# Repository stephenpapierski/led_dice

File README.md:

# led_dice
Embedded code for an LED dice running on an ATtiny85

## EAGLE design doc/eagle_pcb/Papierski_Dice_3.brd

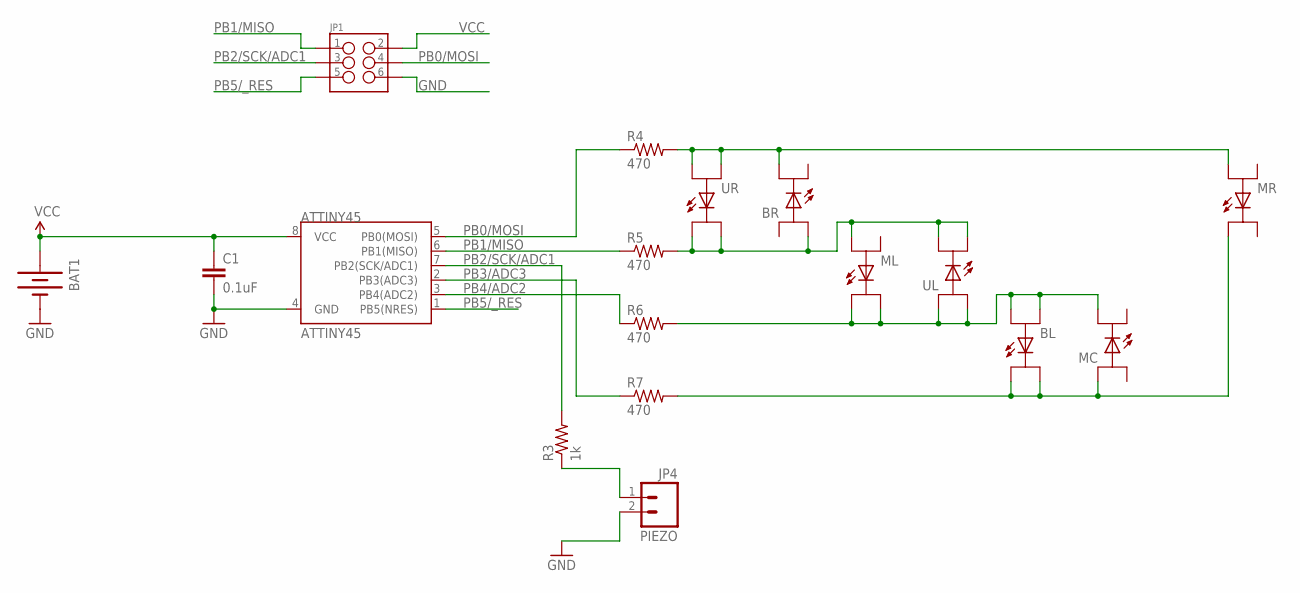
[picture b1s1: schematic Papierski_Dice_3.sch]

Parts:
ATTINY45: ATTINY45; SO08-EIAJ
BAT1: BATTERY20PTH; BATTCOM_20MM_PTH
BL: LED_PIRANHA_5MM_SNGLS; LED_PIRANHA_5MM_SNGL_SMD
BR: LED_PIRANHA_5MM_SNGLS; LED_PIRANHA_5MM_SNGL_SMD
C1: 0.1uF; 0805
JP1: M03X2NO_SILK; 2X3-NS
MC: LED_PIRANHA_5MM_SNGLS; LED_PIRANHA_5MM_SNGL_SMD
ML: LED_PIRANHA_5MM_SNGLS; LED_PIRANHA_5MM_SNGL_SMD
MR: LED_PIRANHA_5MM_SNGLS; LED_PIRANHA_5MM_SNGL_SMD
PIEZO: JP4; 1X02
R3: 1k; AXIAL-0.3
R4, R5, R6: 470; AXIAL-0.3
R7: 470; 0805
UL: LED_PIRANHA_5MM_SNGLS; LED_PIRANHA_5MM_SNGL_SMD
UR: LED_PIRANHA_5MM_SNGLS; LED_PIRANHA_5MM_SNGL_SMD

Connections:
GND: ATTINY45.4 (GND), BAT1.2 (-), C1.2, JP1.6, PIEZO.2
unnamed: BR.K1 (C1), MR.A1, R4.P$2 (2), UR.A1, UR.A2
unnamed: BL.A1, BL.A2, MC.K1 (C1), ML.K1 (C1), ML.K2 (C2), R6.P$2 (2), UL.A1, UL.A2
unnamed: BL.K1 (C1), BL.K2 (C2), MC.A2, MR.K2 (C2), R7.2
unnamed: PIEZO.1, R3.P$1 (1)
unnamed: BR.A1, ML.A1, R5.P$2 (2), UL.K1 (C1), UL.K2 (C2), UR.K1 (C1), UR.K2 (C2)
PB0/MOSI: ATTINY45.5 (PB0(MOSI)), JP1.4, R4.P$1 (1)
PB1/MISO: ATTINY45.6 (PB1(MISO)), JP1.1, R5.P$1 (1)
PB2/SCK/ADC1: ATTINY45.7 (PB2(SCK/ADC1)), JP1.3, R3.P$2 (2)
PB3/ADC3: ATTINY45.2 (PB3(ADC3)), R7.1
PB4/ADC2: ATTINY45.3 (PB4(ADC2)), R6.P$1 (1)
PB5/_RES: ATTINY45.1 (PB5(NRES)), JP1.5
VCC: ATTINY45.8 (VCC), BAT1.1 (+), C1.1, JP1.2

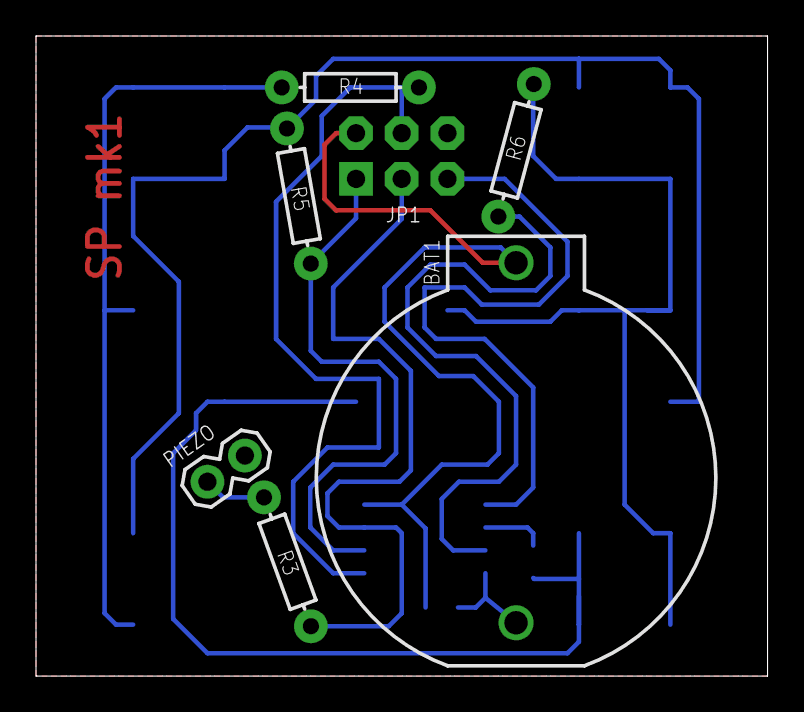
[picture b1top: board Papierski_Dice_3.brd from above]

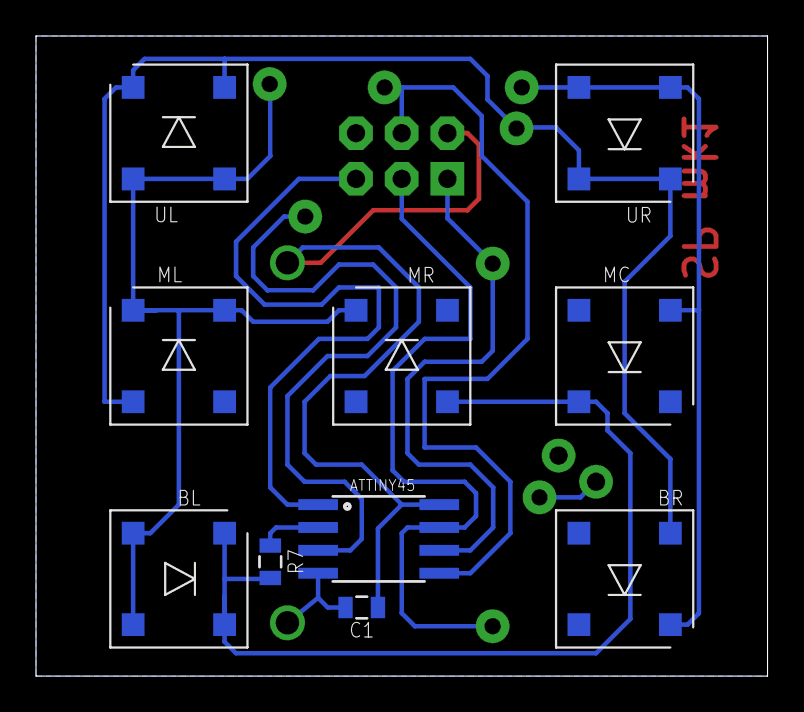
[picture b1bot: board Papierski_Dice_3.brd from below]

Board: 2 copper layers, 40.6 x 35.6 mm, 17 parts (10 on the bottom side), 13 nets.

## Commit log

2015-02-28 Initial setup
2015-02-28 Set up Timer0 and PIEZO External interrupts, and general structure set up
2015-02-28 Configured dice faces, rolls through faces on piezo impact
2015-03-25 Began to restructure code
2015-04-04 Finished code restructure
2015-04-04 Electronic/mechanical project files added
2015-04-07 Added switch debounce
2015-04-08 Setup for dice to operate in different modes
2015-04-12 Updated schematic to specify where each led was physically
2015-04-12 Added ATtiny85 data sheet and folder structure doc
2015-04-12 Added documentation for finite state machine implementations
2015-04-12 Implemented FSM for piezo debounce
2015-04-12 Added image files of schematic and board
2015-04-12 Added "rolling state" to UI finite state machine
2015-04-12 Implemented UI finite state machine; works to roll 1 or 2 numbers
2015-04-14 Modified FSM to remove delay previously necessary to enter single roll mode
2015-04-16 Enabled MCU power-down for power saving
2015-04-18 Cleaned up main loop, added power and dice library
2015-04-18 documentation/clean up
2015-04-23 cleaned up state machines

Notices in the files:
parts and their libraries:
SparkFun-DigitalIC: Licensing: CC v3.0 Share-Alike You are welcome to use this library for commercial purposes.
